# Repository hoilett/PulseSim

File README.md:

# PulseSim
A recreation of the (heart) pulse waveform using discrete components and no processing (microcontroller)

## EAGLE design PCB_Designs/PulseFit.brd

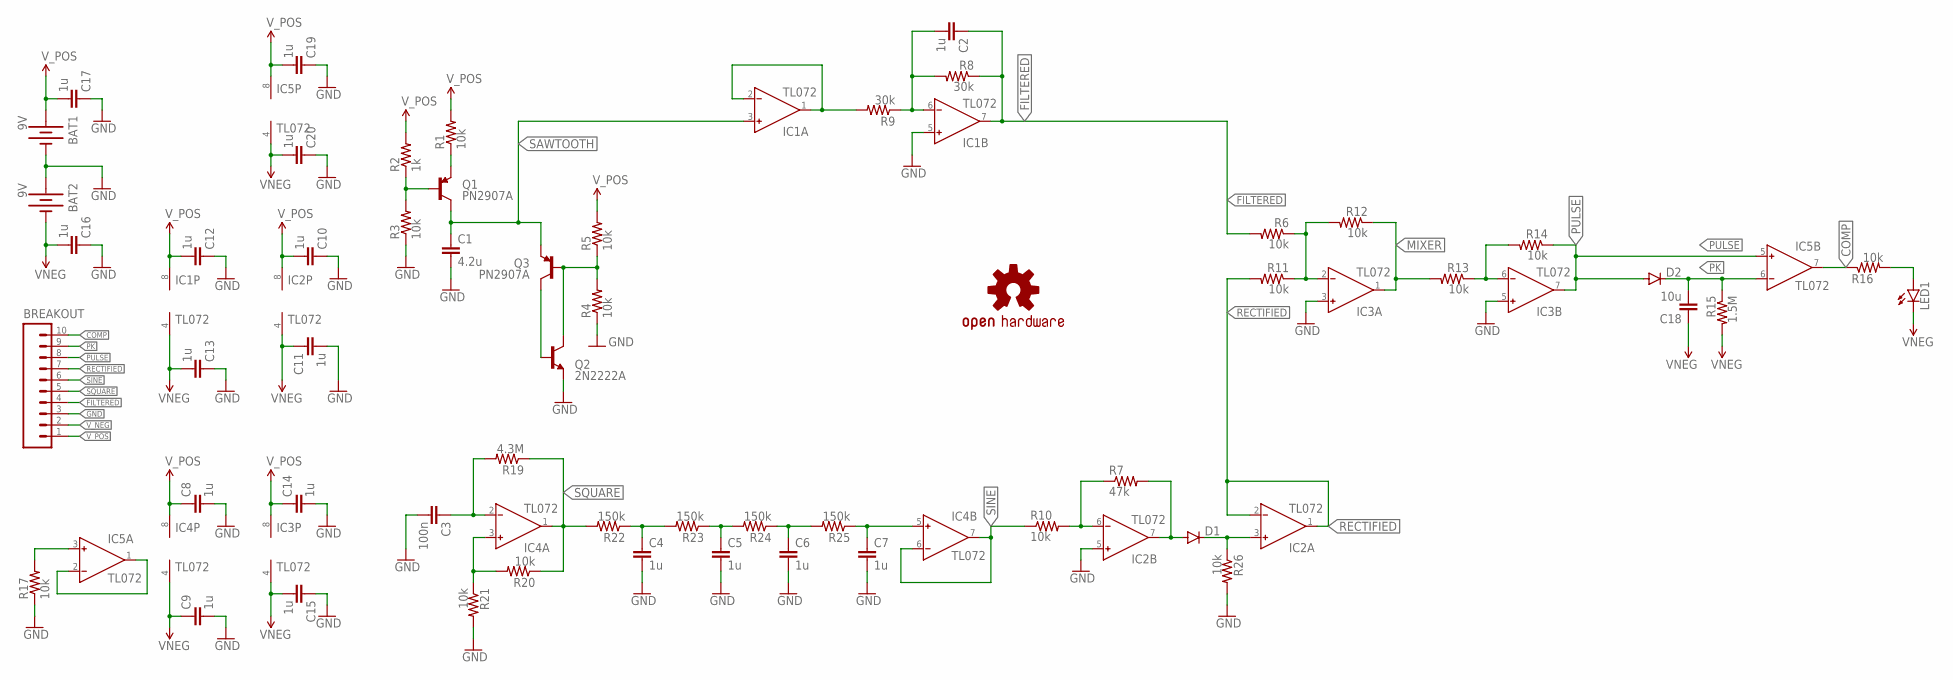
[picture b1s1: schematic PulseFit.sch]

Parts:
BAT1, BAT2: 9V; BATTCON_9V
BREAKOUT: M10NO_SILK_PTH_FEMALE; 1X10_NO_SILK
C1: 4.2u; C0402
C2, C4, C5, C6, C7, C8, C9, C10, C11, C12, C13, C14, C15, C16, C17, C19, C20: 1u; C0402
C3: 100n; C0402
C18: 10u; C0402
D1, D2: 250mA/100V; SOD-323
IC1, IC2, IC3, IC4, IC5: TL072; SO8
LED1: LED1206-BOTTOM; LED-1206-BOTTOM
LOGO1: OSHW-LOGOS; OSHW-LOGO-S
Q1, Q3: PN2907A; SOT23-3
Q2: 2N2222A; SOT23-3
R1, R3, R4, R5, R6, R10, R11, R12, R13, R14, R16, R17, R20, R21, R26: 10k; R0402
R2: 1k; R0402
R7: 47k; R0402
R8, R9: 30k; R0402
R15: 1.5M; R0402
R19: 4.3M; R0402
R22, R23, R24, R25: 150k; R0402

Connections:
COMP: BREAKOUT.10, IC5.7 (OUT), R16.1
FILTERED: BREAKOUT.4, C2.1, IC1.7 (OUT), R6.2, R8.1
GND: BAT1.-, BAT2.+, BREAKOUT.3, C1.2, C3.2, C4.2, C5.2, C6.2, C7.2, C8.2, C9.2, C10.1, C11.2, C12.1, C13.1, C14.2, C15.1, C16.1, C17.1, C19.1, C20.1, IC1.5 (IN+), IC2.5 (IN+), IC3.3 (IN+), IC3.5 (IN+), Q2.2 (E), R3.1, R4.1, R17.1, R21.2, R26.2
MIXER: IC3.1 (OUT), R12.1, R13.2
unnamed: Q1.2 (E), R1.1
unnamed: IC3.6 (IN-), R13.1, R14.2
unnamed: Q1.1 (B), R2.1, R3.2
unnamed: Q2.3 (C), Q3.1 (B), R4.2, R5.1
unnamed: Q2.1 (B), Q3.3 (C)
unnamed: IC1.1 (OUT), IC1.2 (IN-), R9.2
unnamed: IC3.2 (IN-), R6.1, R11.1, R12.2
unnamed: LED1.A, R16.2
unnamed: C2.2, IC1.6 (IN-), R8.2, R9.1
unnamed: IC5.1 (OUT), IC5.2 (IN-)
unnamed: IC5.3 (IN+), R17.2
unnamed: C3.1, IC4.2 (IN-), R19.2
unnamed: IC4.3 (IN+), R20.2, R21.1
unnamed: C6.1, R24.1, R25.2
unnamed: C4.1, R22.1, R23.2
unnamed: C7.1, IC4.5 (IN+), R25.1
unnamed: C5.1, R23.1, R24.2
unnamed: D1.C, IC2.3 (IN+), R26.1
unnamed: IC2.6 (IN-), R7.1, R10.2
unnamed: D1.A, IC2.7 (OUT), R7.2
PK: BREAKOUT.9, C18.2, D2.C, IC5.6 (IN-), R15.1
PULSE: BREAKOUT.8, D2.A, IC3.7 (OUT), IC5.5 (IN+), R14.1
RECTIFIED: BREAKOUT.7, IC2.1 (OUT), IC2.2 (IN-), R11.2
SAWTOOTH: C1.1, IC1.3 (IN+), Q1.3 (C), Q3.2 (E)
SINE: BREAKOUT.6, IC4.6 (IN-), IC4.7 (OUT), R10.1
SQUARE: BREAKOUT.5, IC4.1 (OUT), R19.1, R20.1, R22.2
VNEG: BAT2.-, C16.2, C18.1, C20.2, IC5.4 (V-), LED1.C, R15.2
V_BATT: BAT1.+, C8.1, C12.2, C14.1, C17.2, C19.2, IC1.8 (V+), IC3.8 (V+), IC4.8 (V+), IC5.8 (V+)
V_NEG: BREAKOUT.2, C9.1, C11.1, C13.2, C15.2, IC1.4 (V-), IC2.4 (V-), IC3.4 (V-), IC4.4 (V-)
V_POS: BREAKOUT.1, C10.2, IC2.8 (V+), R1.2, R2.2, R5.2

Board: 2 copper layers, 60 parts (0 on the bottom side), 34 nets, no tracks yet.

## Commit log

2016-08-24 hello world
2016-08-28 schematic is finished, board needs more work

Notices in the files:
PCB_Designs/PulseFit.sch:
Creative Commons License
parts and their libraries:
SparkFun-DiscreteSemi: Licensing: Creative Commons ShareAlike 4.0 International - https://creativecommons.org/licenses/by-sa/4.0
